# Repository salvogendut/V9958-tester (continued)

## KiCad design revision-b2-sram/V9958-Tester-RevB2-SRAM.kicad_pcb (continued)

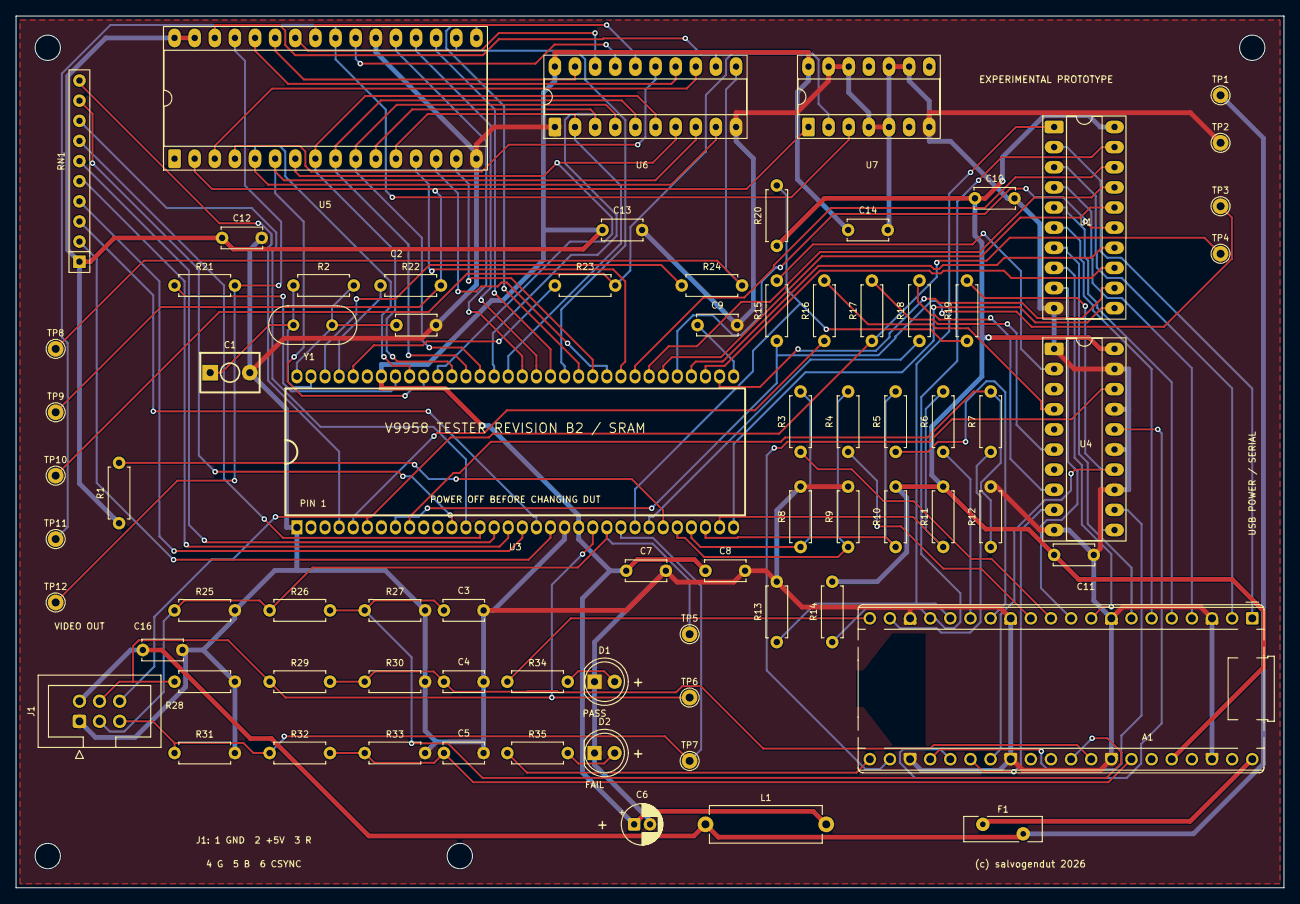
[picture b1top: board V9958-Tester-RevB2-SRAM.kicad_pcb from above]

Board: 2 copper layers, 160.0 x 110.0 mm, 80 parts (0 on the bottom side), 104 nets.

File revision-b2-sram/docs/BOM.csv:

Quantity,References,Value / part,KiCad footprint
1,A1,Raspberry Pi Pico,Module:RaspberryPi_Pico_Common_THT
1,C1,30pF trimmer,V9958-Tester:C_Trim_P5.00mm
1,C10,100n U1,Capacitor_THT:C_Disc_D5.0mm_W2.5mm_P5.00mm
1,C11,100n U4,Capacitor_THT:C_Disc_D5.0mm_W2.5mm_P5.00mm
1,C12,100n SRAM,Capacitor_THT:C_Disc_D5.0mm_W2.5mm_P5.00mm
1,C13,100n U6,Capacitor_THT:C_Disc_D5.0mm_W2.5mm_P5.00mm
1,C14,100n U7,Capacitor_THT:C_Disc_D5.0mm_W2.5mm_P5.00mm
1,C16,100n VIDEO,Capacitor_THT:C_Disc_D5.0mm_W2.5mm_P5.00mm
1,C2,22pF,Capacitor_THT:C_Disc_D5.0mm_W2.5mm_P5.00mm
3,C3 C4 C5,10n,Capacitor_THT:C_Disc_D5.0mm_W2.5mm_P5.00mm
1,C6,100uF,Capacitor_THT:CP_Radial_D5.0mm_P2.00mm
1,C7,100n VDP,Capacitor_THT:C_Disc_D5.0mm_W2.5mm_P5.00mm
1,C8,100n DAC,Capacitor_THT:C_Disc_D5.0mm_W2.5mm_P5.00mm
1,C9,100n VBB,Capacitor_THT:C_Disc_D5.0mm_W2.5mm_P5.00mm
1,D1,GREEN PASS,LED_THT:LED_D5.0mm
1,D2,RED FAIL,LED_THT:LED_D5.0mm
1,F1,Bourns MF-RHT100 PTC 1.0A,Fuse:Fuse_Bourns_MF-RHT100
1,J1,VIDEO DAUGHTERBOARD,Connector_IDC:IDC-Header_2x03_P2.54mm_Vertical
1,L1,5.6uH,Inductor_THT:L_Axial_L14.0mm_D4.5mm_P15.24mm_Horizontal_Fastron_LACC
9,R1 R8 R9 R10 R11 R12 R13 R14 R20,10k,Resistor_THT:R_Axial_DIN0207_L6.3mm_D2.5mm_P7.62mm_Horizontal
7,R15 R16 R17 R18 R19 R34 R35,1k,Resistor_THT:R_Axial_DIN0207_L6.3mm_D2.5mm_P7.62mm_Horizontal
1,R2,470k,Resistor_THT:R_Axial_DIN0207_L6.3mm_D2.5mm_P7.62mm_Horizontal
4,R21 R22 R23 R24,47,Resistor_THT:R_Axial_DIN0207_L6.3mm_D2.5mm_P7.62mm_Horizontal
3,R25 R28 R31,470,Resistor_THT:R_Axial_DIN0207_L6.3mm_D2.5mm_P7.62mm_Horizontal
6,R26 R27 R29 R30 R32 R33,22k,Resistor_THT:R_Axial_DIN0207_L6.3mm_D2.5mm_P7.62mm_Horizontal
5,R3 R4 R5 R6 R7,330,Resistor_THT:R_Axial_DIN0207_L6.3mm_D2.5mm_P7.62mm_Horizontal
1,RN1,10k bussed,Resistor_THT:R_Array_SIP10
1,U1,SN74LVC245AN,Package_DIP:DIP-20_W7.62mm_Socket_LongPads
1,U3,V9958 DUT,V9958-Tester:SDIP-64_W19.05mm_P1.778mm_Socket
1,U4,SN74LVC244AN,Package_DIP:DIP-20_W7.62mm_Socket_LongPads
1,U5,AS6C1008-55PCN 128Kx8 SRAM,Package_DIP:DIP-32_W15.24mm_Socket_LongPads
1,U6,SN74AHCT573N row-address latch,Package_DIP:DIP-20_W7.62mm_Socket_LongPads
1,U7,SN74AHCT08N CAS-to-OE gate,Package_DIP:DIP-14_W7.62mm_Socket_LongPads
1,Y1,21.477270MHz,Crystal:Crystal_HC49-U_Vertical

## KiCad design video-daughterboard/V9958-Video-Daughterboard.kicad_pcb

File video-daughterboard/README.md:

# V9958 RGB DIN daughterboard

This optional all-through-hole 120 x 80 mm board moves the CXA1645P RGB cable
drivers and Omega-compatible DIN-8 connector away from the minimal Revision B
tester core.

J1 uses a keyed straight-through 2x3 IDC cable: 1 GND, 2 +5 V, 3 red, 4 green,
5 blue and 6 CSYNC. J2 follows the Omega RGB assignments: pin 1 GND, pin 3 AV
control, pin 4 composite sync, pin 5 RGB/YS control, pin 6 red, pin 7 green and
pin 8 blue. Pin 2 is unconnected because the tester has no audio source.

The output is native 15.6 kHz PAL RGB, not VGA. The board does not create
composite video; J2 pin 4 is sync only. See the [schematic PDF](docs/V9958-Video-Daughterboard-Schematic.pdf),
[BOM](docs/BOM.csv), [test procedure](docs/TEST-PROCEDURE.md) and
[validation record](docs/VALIDATION.md). This remains an unbuilt prototype.

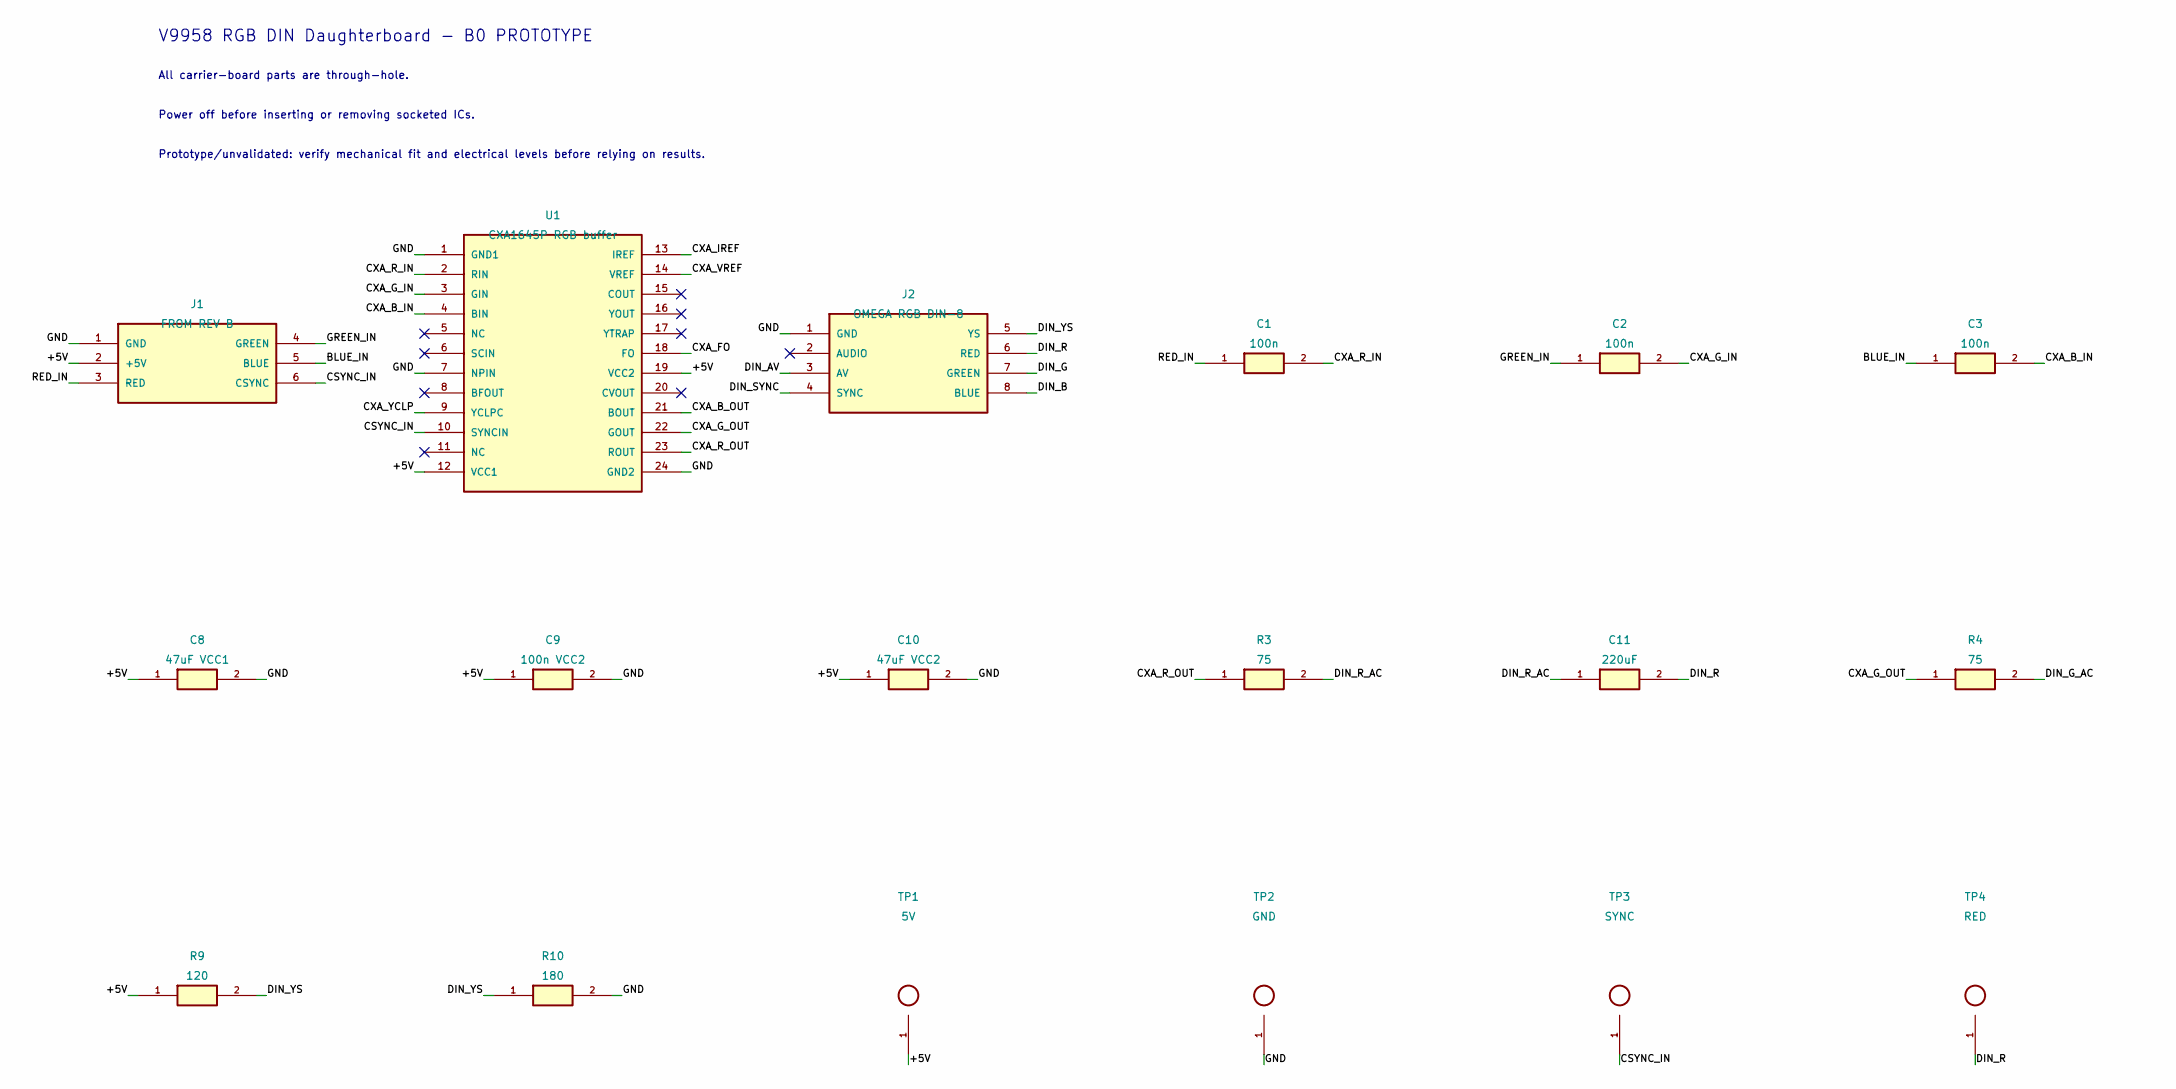
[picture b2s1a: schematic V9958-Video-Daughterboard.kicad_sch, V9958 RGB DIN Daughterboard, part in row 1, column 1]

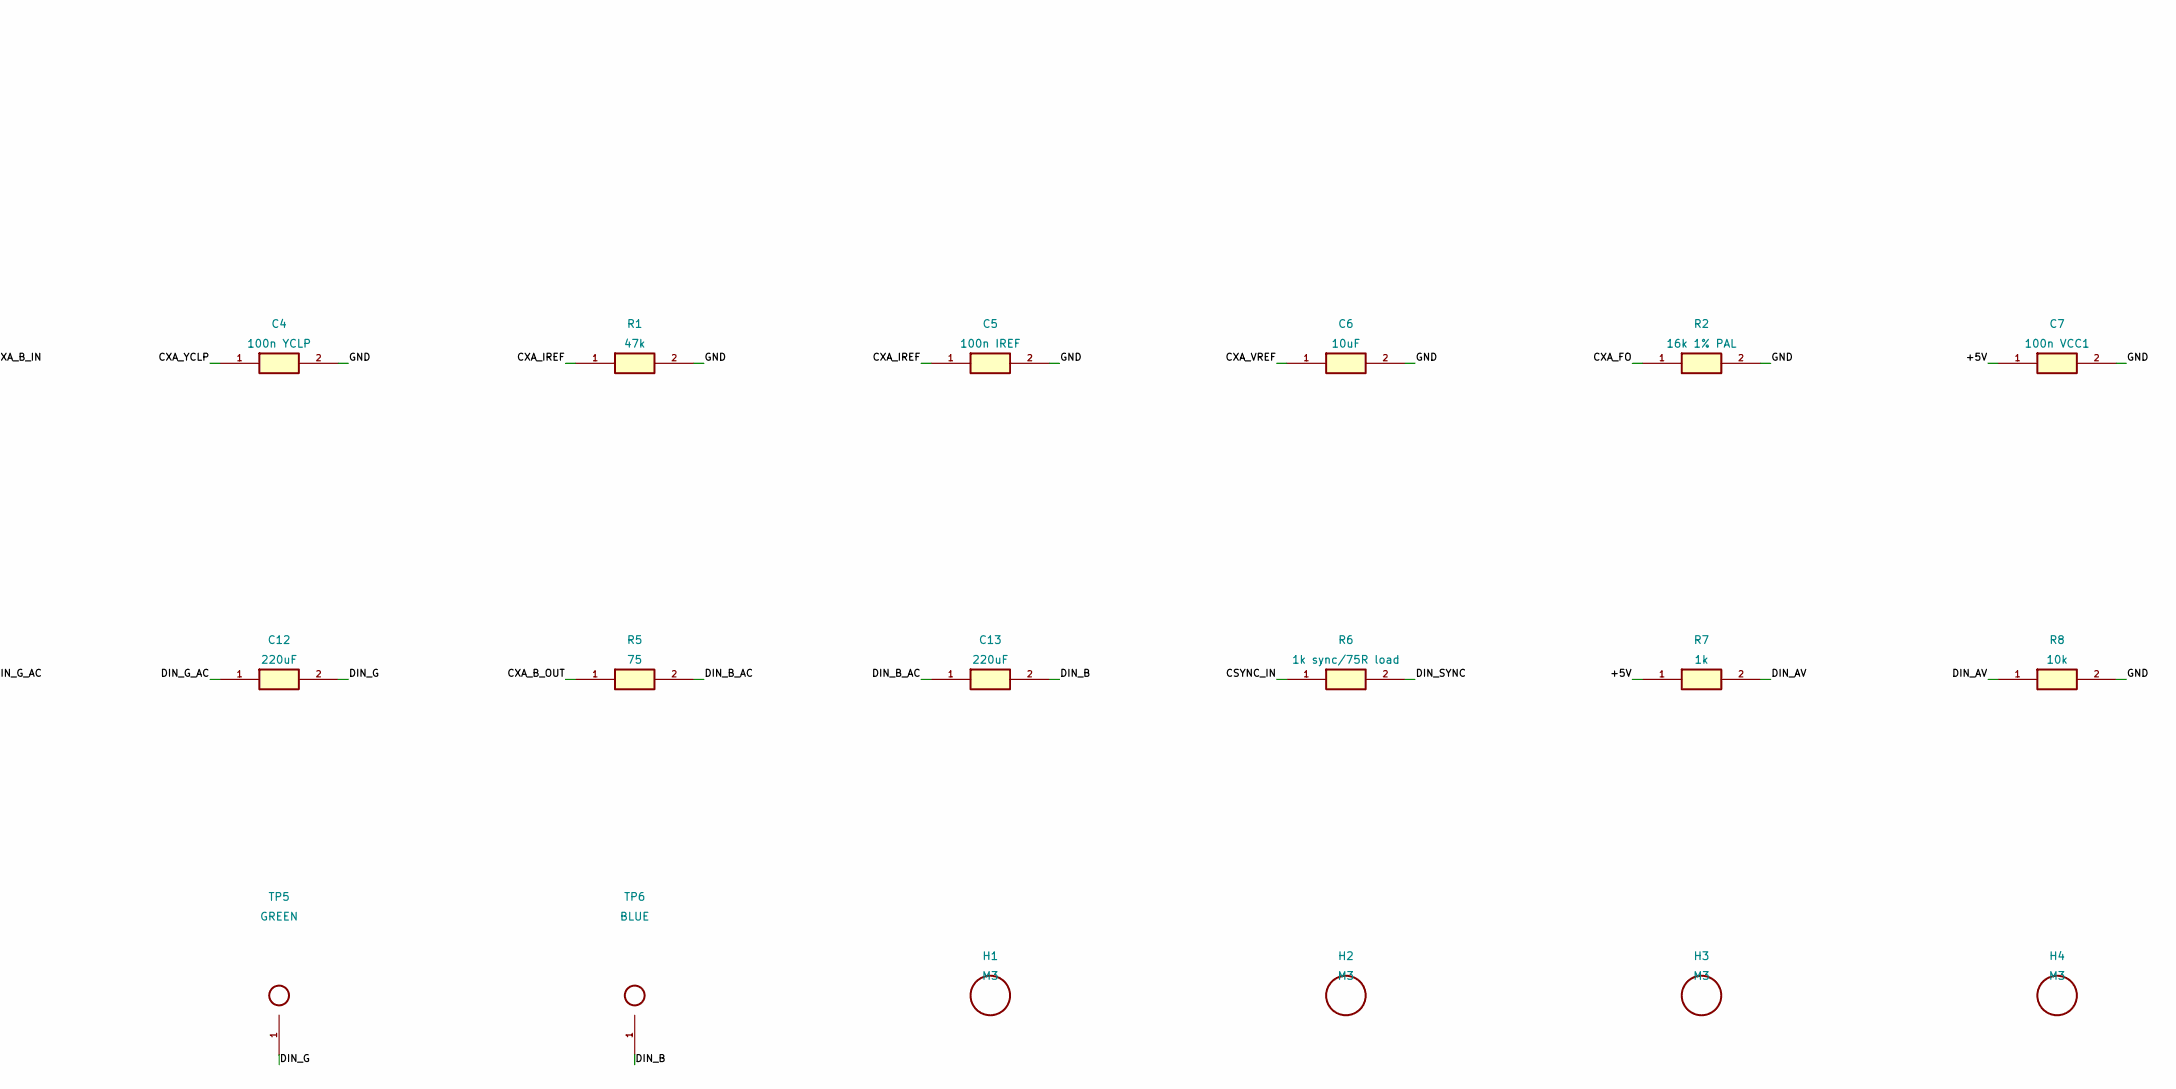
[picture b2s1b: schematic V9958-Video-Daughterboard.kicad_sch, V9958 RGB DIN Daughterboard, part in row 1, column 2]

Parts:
C1, C2, C3: 100n; C_Disc_D5.0mm_W2.5mm_P5.00mm
C4: 100n YCLP; C_Disc_D5.0mm_W2.5mm_P5.00mm
C5: 100n IREF; C_Disc_D5.0mm_W2.5mm_P5.00mm
C6: 10uF; CP_Radial_D5.0mm_P2.00mm
C7: 100n VCC1; C_Disc_D5.0mm_W2.5mm_P5.00mm
C8: 47uF VCC1; CP_Radial_D5.0mm_P2.00mm
C9: 100n VCC2; C_Disc_D5.0mm_W2.5mm_P5.00mm
C10: 47uF VCC2; CP_Radial_D5.0mm_P2.00mm
C11, C12, C13: 220uF; CP_Radial_D8.0mm_P3.50mm
H1, H2, H3, H4: M3; MountingHole_3.2mm_M3
J1: FROM REV B; IDC-Header_2x03_P2.54mm_Vertical
J2: OMEGA RGB DIN-8; DIN8_Omega_THT
R1: 47k; R_Axial_DIN0207_L6.3mm_D2.5mm_P7.62mm_Horizontal
R2: 16k 1% PAL; R_Axial_DIN0207_L6.3mm_D2.5mm_P7.62mm_Horizontal
R3, R4, R5: 75; R_Axial_DIN0207_L6.3mm_D2.5mm_P7.62mm_Horizontal
R6: 1k sync/75R load; R_Axial_DIN0207_L6.3mm_D2.5mm_P7.62mm_Horizontal
R7: 1k; R_Axial_DIN0207_L6.3mm_D2.5mm_P7.62mm_Horizontal
R8: 10k; R_Axial_DIN0207_L6.3mm_D2.5mm_P7.62mm_Horizontal
R9: 120; R_Axial_DIN0207_L6.3mm_D2.5mm_P7.62mm_Horizontal
R10: 180; R_Axial_DIN0207_L6.3mm_D2.5mm_P7.62mm_Horizontal
TP1: 5V; TestPoint_THTPad_D2.0mm_Drill1.0mm
TP2: GND; TestPoint_THTPad_D2.0mm_Drill1.0mm
TP3: SYNC; TestPoint_THTPad_D2.0mm_Drill1.0mm
TP4: RED; TestPoint_THTPad_D2.0mm_Drill1.0mm
TP5: GREEN; TestPoint_THTPad_D2.0mm_Drill1.0mm
TP6: BLUE; TestPoint_THTPad_D2.0mm_Drill1.0mm
U1: CXA1645P RGB buffer; DIP-24_W10.16mm_Socket_LongPads

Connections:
/+5V: C7.1, C8.1, C9.1, C10.1, J1.2 (+5V), R7.1, R9.1, TP1.1, U1.12 (VCC1), U1.19 (VCC2)
/BLUE_IN: C3.1, J1.5 (BLUE)
/CSYNC_IN: J1.6 (CSYNC), R6.1, TP3.1, U1.10 (SYNCIN)
/CXA_B_IN: C3.2, U1.4 (BIN)
/CXA_B_OUT: R5.1, U1.21 (BOUT)
/CXA_FO: R2.1, U1.18 (FO)
/CXA_G_IN: C2.2, U1.3 (GIN)
/CXA_G_OUT: R4.1, U1.22 (GOUT)
/CXA_IREF: C5.1, R1.1, U1.13 (IREF)
/CXA_R_IN: C1.2, U1.2 (RIN)
/CXA_R_OUT: R3.1, U1.23 (ROUT)
/CXA_VREF: C6.1, U1.14 (VREF)
/CXA_YCLP: C4.1, U1.9 (YCLPC)
/DIN_AV: J2.3 (AV), R7.2, R8.1
/DIN_B: C13.2, J2.8 (BLUE), TP6.1
/DIN_B_AC: C13.1, R5.2
/DIN_G: C12.2, J2.7 (GREEN), TP5.1
/DIN_G_AC: C12.1, R4.2
/DIN_R: C11.2, J2.6 (RED), TP4.1
/DIN_R_AC: C11.1, R3.2
/DIN_SYNC: J2.4 (SYNC), R6.2
/DIN_YS: J2.5 (YS), R9.2, R10.1
/GND: C4.2, C5.2, C6.2, C7.2, C8.2, C9.2, C10.2, J1.1 (GND), J2.1 (GND), R1.2, R2.2, R8.2, R10.2, TP2.1, U1.1 (GND1), U1.7 (NPIN), U1.24 (GND2)
/GREEN_IN: C2.1, J1.4 (GREEN)
/RED_IN: C1.1, J1.3 (RED)

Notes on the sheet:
V9958 RGB DIN Daughterboard - B0 PROTOTYPE
All carrier-board parts are through-hole.
Power off before inserting or removing socketed ICs.
Prototype/unvalidated: verify mechanical fit and electrical levels before relying on results.

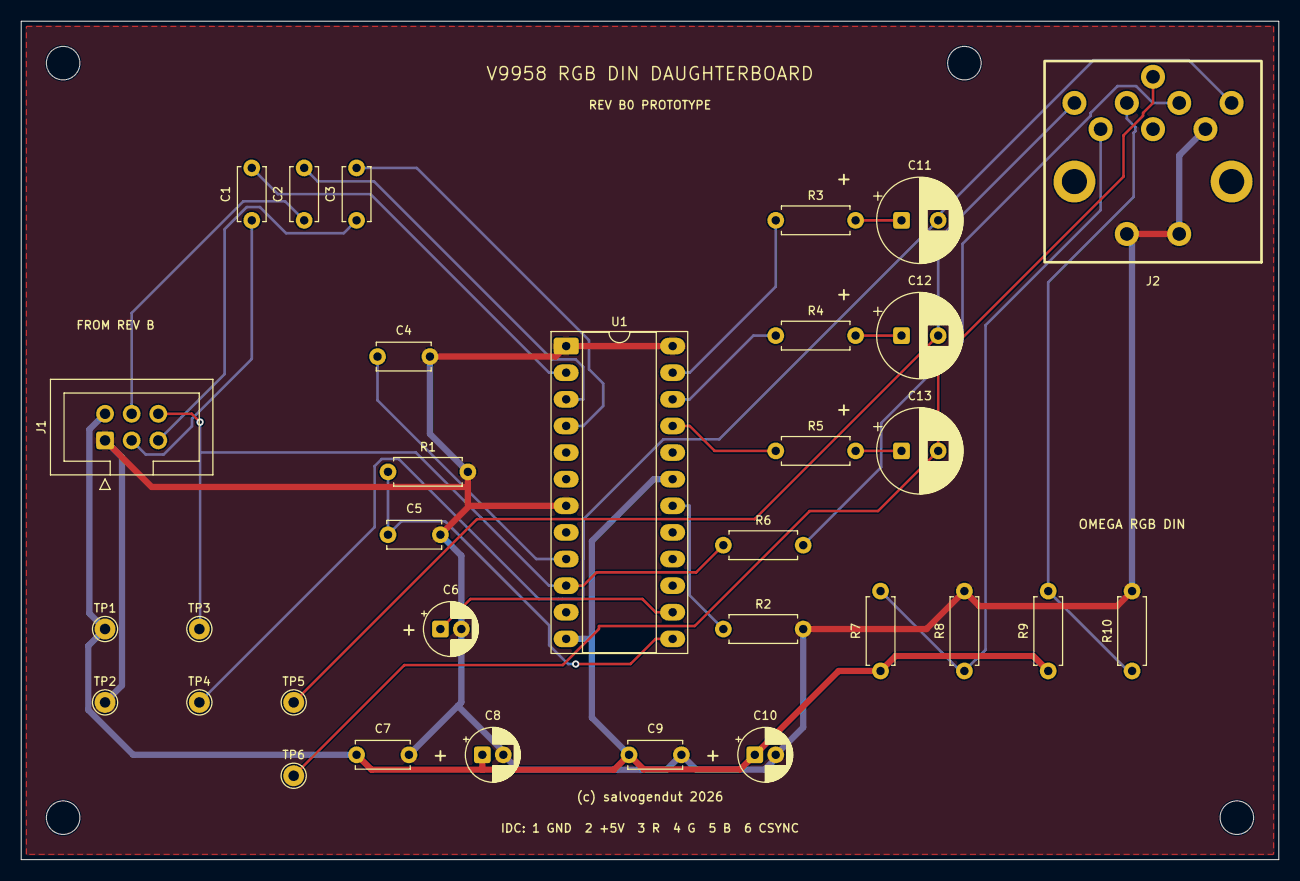
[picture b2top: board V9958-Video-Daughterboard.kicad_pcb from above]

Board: 2 copper layers, 120.0 x 80.0 mm, 36 parts (0 on the bottom side), 25 nets.

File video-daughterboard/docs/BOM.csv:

Quantity,References,Value / part,KiCad footprint
3,C1 C2 C3,100n,Capacitor_THT:C_Disc_D5.0mm_W2.5mm_P5.00mm
1,C10,47uF VCC2,Capacitor_THT:CP_Radial_D5.0mm_P2.00mm
3,C11 C12 C13,220uF,Capacitor_THT:CP_Radial_D8.0mm_P3.50mm
1,C4,100n YCLP,Capacitor_THT:C_Disc_D5.0mm_W2.5mm_P5.00mm
1,C5,100n IREF,Capacitor_THT:C_Disc_D5.0mm_W2.5mm_P5.00mm
1,C6,10uF,Capacitor_THT:CP_Radial_D5.0mm_P2.00mm
1,C7,100n VCC1,Capacitor_THT:C_Disc_D5.0mm_W2.5mm_P5.00mm
1,C8,47uF VCC1,Capacitor_THT:CP_Radial_D5.0mm_P2.00mm
1,C9,100n VCC2,Capacitor_THT:C_Disc_D5.0mm_W2.5mm_P5.00mm
1,J1,FROM REV B,Connector_IDC:IDC-Header_2x03_P2.54mm_Vertical
1,J2,OMEGA RGB DIN-8,V9958-Video-Daughterboard:DIN8_Omega_THT
1,R1,47k,Resistor_THT:R_Axial_DIN0207_L6.3mm_D2.5mm_P7.62mm_Horizontal
1,R10,180,Resistor_THT:R_Axial_DIN0207_L6.3mm_D2.5mm_P7.62mm_Horizontal
1,R2,16k 1% PAL,Resistor_THT:R_Axial_DIN0207_L6.3mm_D2.5mm_P7.62mm_Horizontal
3,R3 R4 R5,75,Resistor_THT:R_Axial_DIN0207_L6.3mm_D2.5mm_P7.62mm_Horizontal
1,R6,1k sync/75R load,Resistor_THT:R_Axial_DIN0207_L6.3mm_D2.5mm_P7.62mm_Horizontal
1,R7,1k,Resistor_THT:R_Axial_DIN0207_L6.3mm_D2.5mm_P7.62mm_Horizontal
1,R8,10k,Resistor_THT:R_Axial_DIN0207_L6.3mm_D2.5mm_P7.62mm_Horizontal
1,R9,120,Resistor_THT:R_Axial_DIN0207_L6.3mm_D2.5mm_P7.62mm_Horizontal
1,U1,CXA1645P RGB buffer,Package_DIP:DIP-24_W10.16mm_Socket_LongPads

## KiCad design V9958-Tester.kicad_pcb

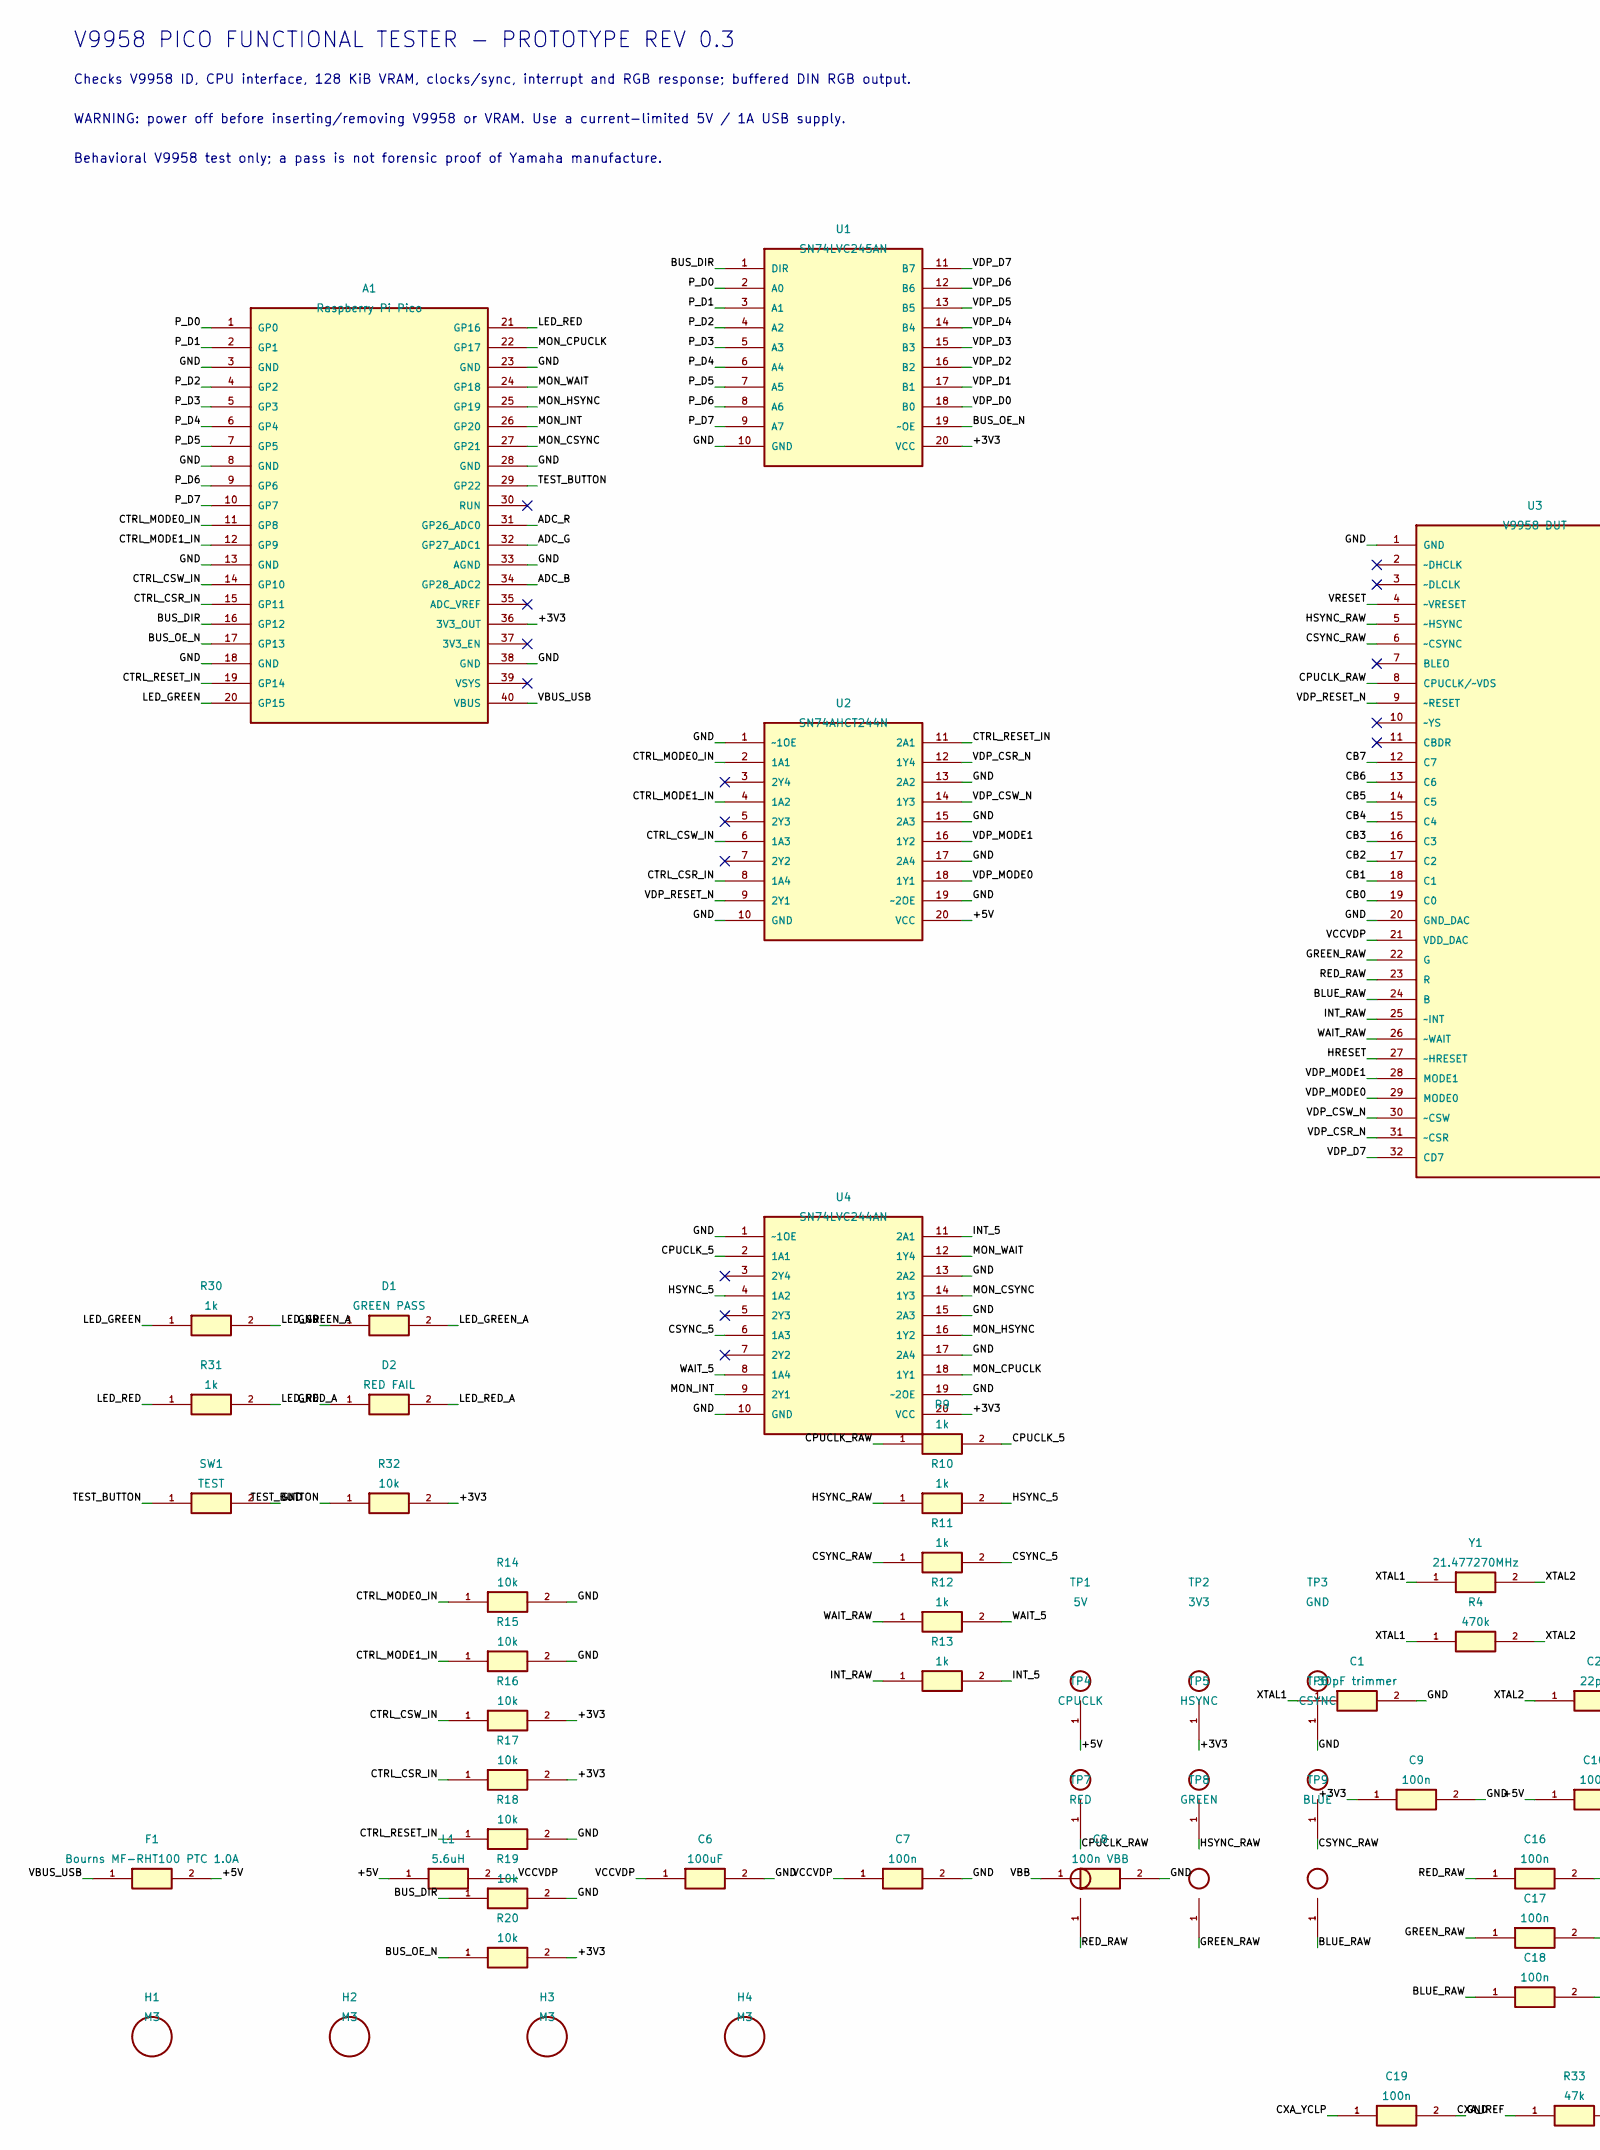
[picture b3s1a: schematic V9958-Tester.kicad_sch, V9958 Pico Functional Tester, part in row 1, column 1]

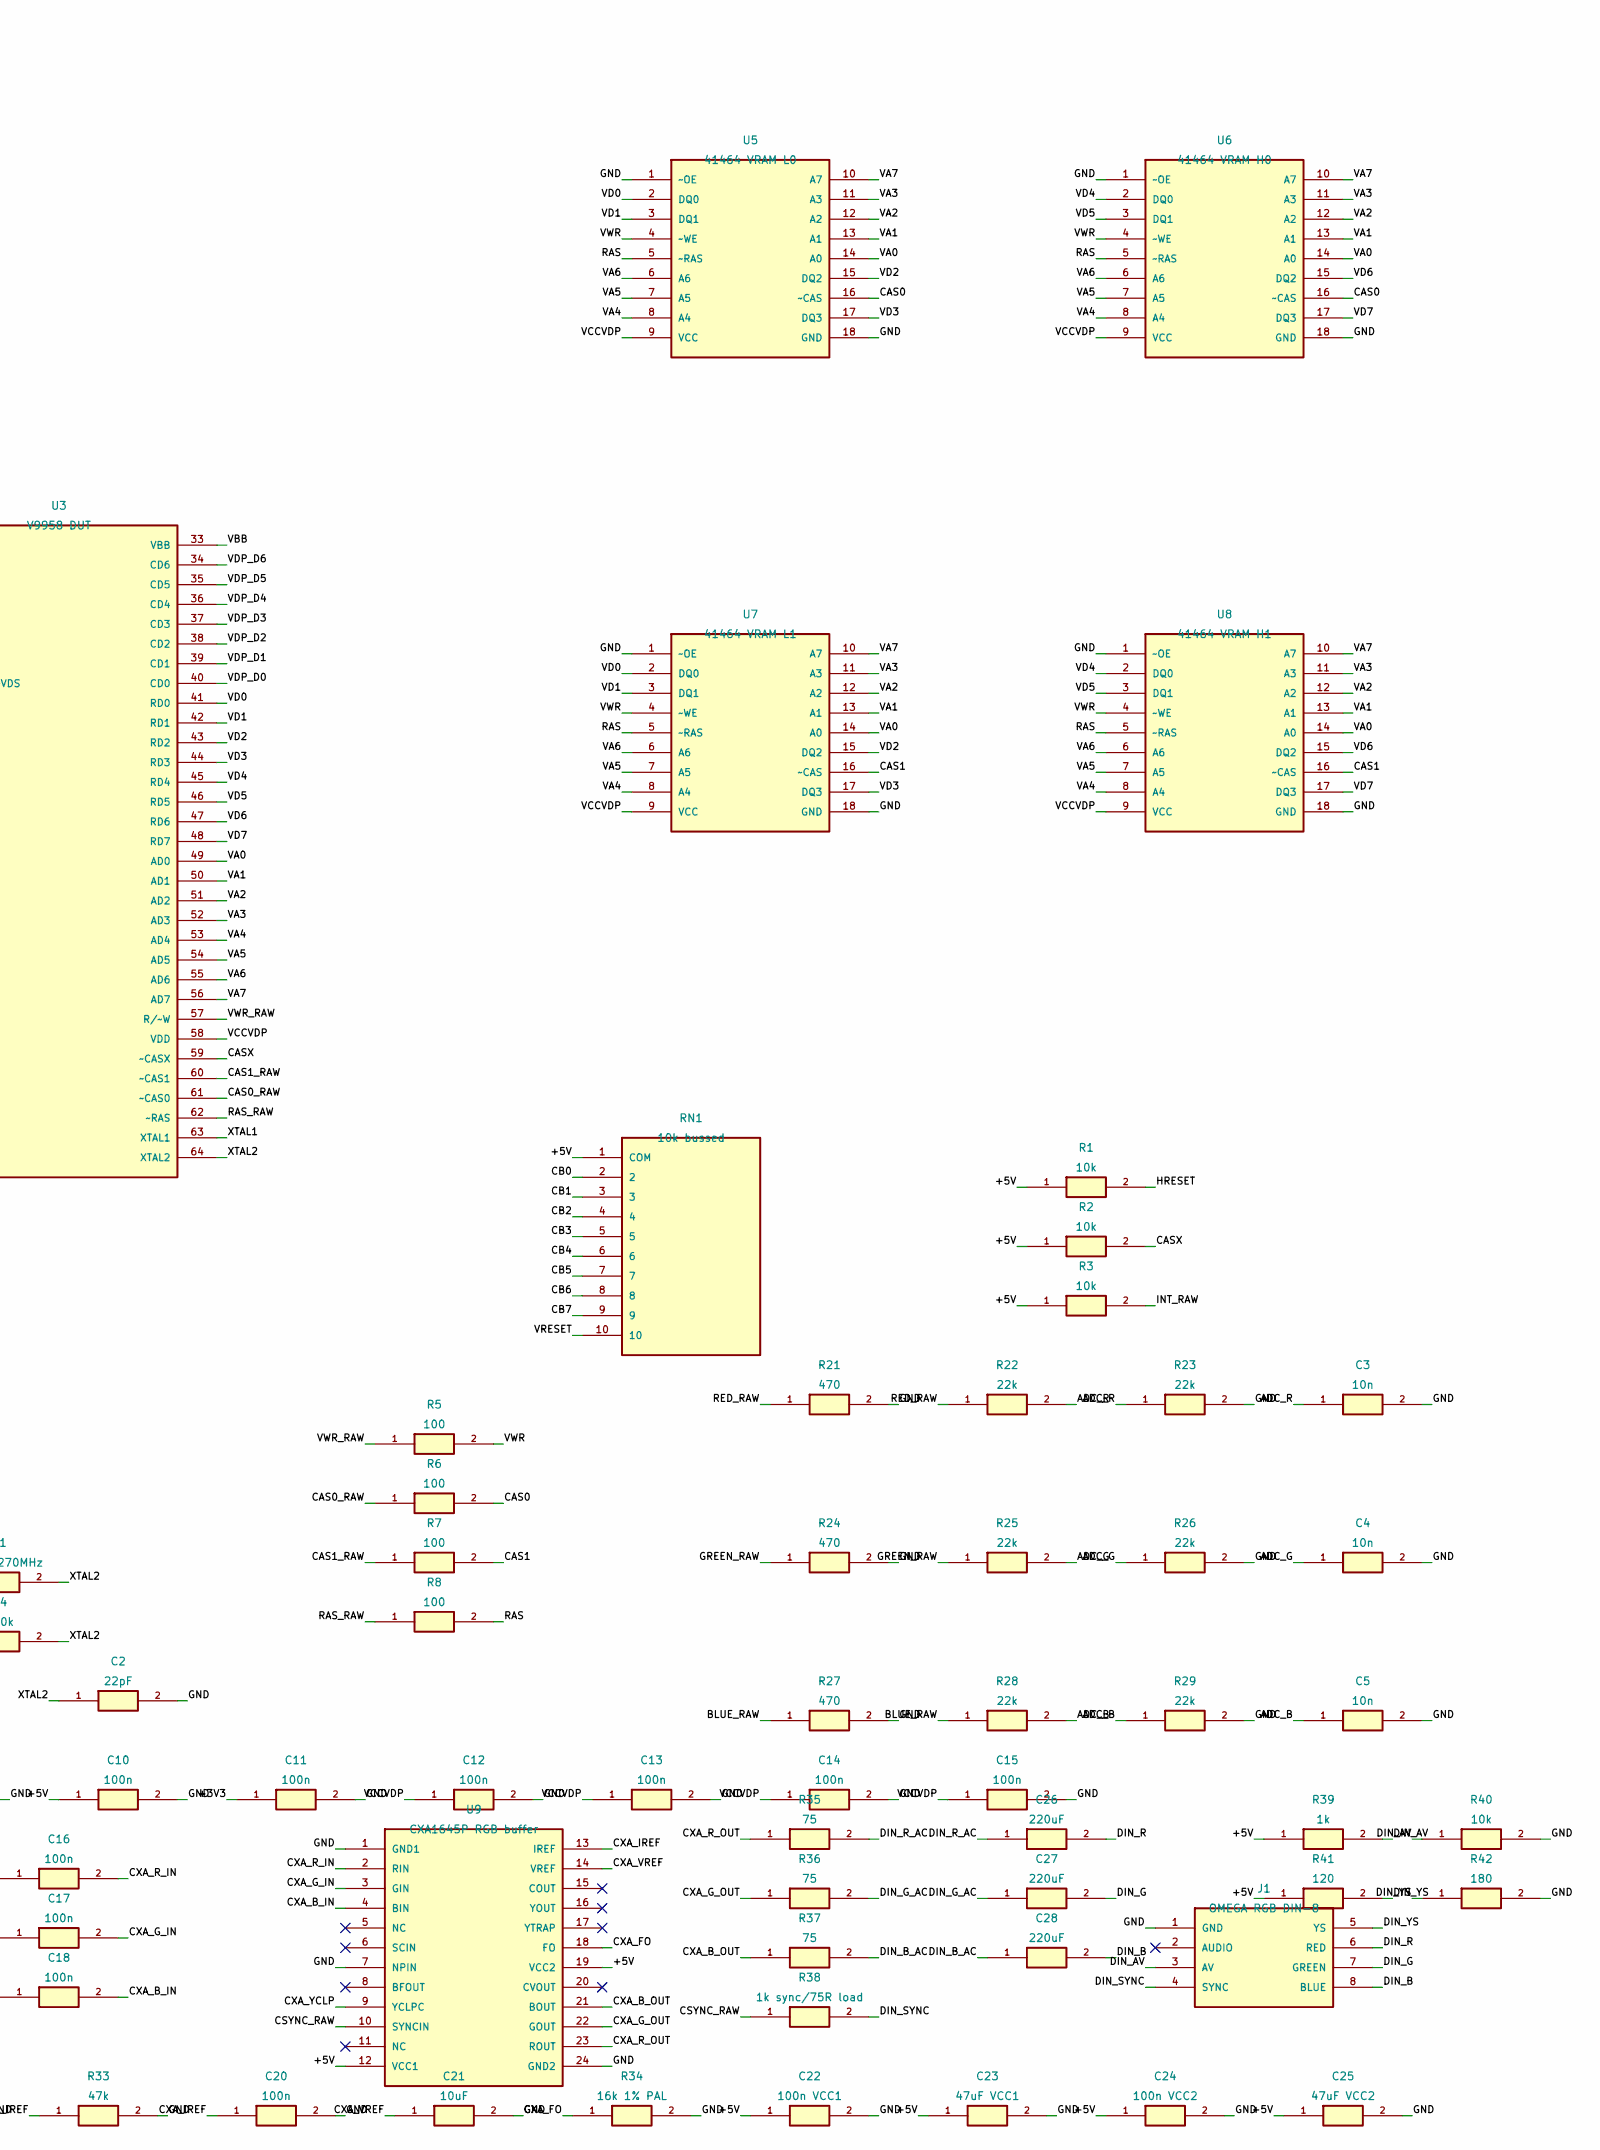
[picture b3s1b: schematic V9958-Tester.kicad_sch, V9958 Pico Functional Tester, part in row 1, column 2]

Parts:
A1: Raspberry Pi Pico; RaspberryPi_Pico_Common_THT
C1: 30pF trimmer; C_Trim_P5.00mm
C2: 22pF; C_Disc_D5.0mm_W2.5mm_P5.00mm
C3, C4, C5: 10n; C_Disc_D5.0mm_W2.5mm_P5.00mm
C6: 100uF; CP_Radial_D5.0mm_P2.00mm
C7, C9, C10, C11, C12, C13, C14, C15, C16, C17, C18, C19, C20: 100n; C_Disc_D5.0mm_W2.5mm_P5.00mm
C8: 100n VBB; C_Disc_D5.0mm_W2.5mm_P5.00mm
C21: 10uF; CP_Radial_D5.0mm_P2.00mm
C22: 100n VCC1; C_Disc_D5.0mm_W2.5mm_P5.00mm
C23: 47uF VCC1; CP_Radial_D5.0mm_P2.00mm
C24: 100n VCC2; C_Disc_D5.0mm_W2.5mm_P5.00mm
C25: 47uF VCC2; CP_Radial_D5.0mm_P2.00mm
C26, C27, C28: 220uF; CP_Radial_D8.0mm_P3.50mm
D1: GREEN PASS; LED_D5.0mm
D2: RED FAIL; LED_D5.0mm
F1: Bourns MF-RHT100 PTC 1.0A; Fuse_Bourns_MF-RHT100
H1, H2, H3, H4: M3; MountingHole_3.2mm_M3
J1: OMEGA RGB DIN-8; DIN8_Omega_THT
L1: 5.6uH; L_Axial_L14.0mm_D4.5mm_P15.24mm_Horizontal_Fastron_LACC
R1, R2, R3, R14, R15, R16, R17, R18, R19, R20, R32, R40: 10k; R_Axial_DIN0207_L6.3mm_D2.5mm_P7.62mm_Horizontal
R4: 470k; R_Axial_DIN0207_L6.3mm_D2.5mm_P7.62mm_Horizontal
R5, R6, R7, R8: 100; R_Axial_DIN0207_L6.3mm_D2.5mm_P7.62mm_Horizontal
R9, R10, R11, R12, R13, R30, R31, R39: 1k; R_Axial_DIN0207_L6.3mm_D2.5mm_P7.62mm_Horizontal
R21, R24, R27: 470; R_Axial_DIN0207_L6.3mm_D2.5mm_P7.62mm_Horizontal
R22, R23, R25, R26, R28, R29: 22k; R_Axial_DIN0207_L6.3mm_D2.5mm_P7.62mm_Horizontal
R33: 47k; R_Axial_DIN0207_L6.3mm_D2.5mm_P7.62mm_Horizontal
R34: 16k 1% PAL; R_Axial_DIN0207_L6.3mm_D2.5mm_P7.62mm_Horizontal
R35, R36, R37: 75; R_Axial_DIN0207_L6.3mm_D2.5mm_P7.62mm_Horizontal
R38: 1k sync/75R load; R_Axial_DIN0207_L6.3mm_D2.5mm_P7.62mm_Horizontal
R41: 120; R_Axial_DIN0207_L6.3mm_D2.5mm_P7.62mm_Horizontal
R42: 180; R_Axial_DIN0207_L6.3mm_D2.5mm_P7.62mm_Horizontal
RN1: 10k bussed; R_Array_SIP10
SW1: TEST; SW_PUSH_6mm_H7.3mm
TP1: 5V; TestPoint_THTPad_D2.0mm_Drill1.0mm
TP2: 3V3; TestPoint_THTPad_D2.0mm_Drill1.0mm
TP3: GND; TestPoint_THTPad_D2.0mm_Drill1.0mm
TP4: CPUCLK; TestPoint_THTPad_D2.0mm_Drill1.0mm
TP5: HSYNC; TestPoint_THTPad_D2.0mm_Drill1.0mm
TP6: CSYNC; TestPoint_THTPad_D2.0mm_Drill1.0mm
TP7: RED; TestPoint_THTPad_D2.0mm_Drill1.0mm
TP8: GREEN; TestPoint_THTPad_D2.0mm_Drill1.0mm
TP9: BLUE; TestPoint_THTPad_D2.0mm_Drill1.0mm
U1: SN74LVC245AN; DIP-20_W7.62mm_Socket_LongPads
U2: SN74AHCT244N; DIP-20_W7.62mm_Socket_LongPads
U3: V9958 DUT; SDIP-64_W19.05mm_P1.778mm_Socket
U4: SN74LVC244AN; DIP-20_W7.62mm_Socket_LongPads
U5: 41464 VRAM L0; DIP-18_W7.62mm_Socket_LongPads
U6: 41464 VRAM H0; DIP-18_W7.62mm_Socket_LongPads
U7: 41464 VRAM L1; DIP-18_W7.62mm_Socket_LongPads
U8: 41464 VRAM H1; DIP-18_W7.62mm_Socket_LongPads
U9: CXA1645P RGB buffer; DIP-24_W10.16mm_Socket_LongPads
Y1: 21.477270MHz; Crystal_HC49-U_Vertical

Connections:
/+3V3: A1.36 (3V3_OUT), C9.1, C11.1, R16.2, R17.2, R20.2, R32.2, TP2.1, U1.20 (VCC), U4.20 (VCC)
/+5V: C10.1, C22.1, C23.1, C24.1, C25.1, F1.2, L1.1, R1.1, R2.1, R3.1, R39.1, R41.1, RN1.1 (COM), TP1.1, U2.20 (VCC), U9.12 (VCC1), U9.19 (VCC2)
/ADC_B: A1.34 (GP28_ADC2), C5.1, R28.2, R29.1
/ADC_G: A1.32 (GP27_ADC1), C4.1, R25.2, R26.1
/ADC_R: A1.31 (GP26_ADC0), C3.1, R22.2, R23.1
/BLUE_RAW: C18.1, R27.1, R28.1, TP9.1, U3.24 (B)
/BUS_DIR: A1.16 (GP12), R19.1, U1.1 (DIR)
/BUS_OE_N: A1.17 (GP13), R20.1, U1.19 (~OE)
/CAS0: R6.2, U5.16 (~CAS), U6.16 (~CAS)
/CAS0_RAW: R6.1, U3.61 (~CAS0)
/CAS1: R7.2, U7.16 (~CAS), U8.16 (~CAS)
/CAS1_RAW: R7.1, U3.60 (~CAS1)
/CASX: R2.2, U3.59 (~CASX)
/CB0: RN1.2, U3.19 (C0)
/CB1: RN1.3, U3.18 (C1)
/CB2: RN1.4, U3.17 (C2)
/CB3: RN1.5, U3.16 (C3)
/CB4: RN1.6, U3.15 (C4)
/CB5: RN1.7, U3.14 (C5)
/CB6: RN1.8, U3.13 (C6)
/CB7: RN1.9, U3.12 (C7)
/CPUCLK_5: R9.2, U4.2 (1A1)
/CPUCLK_RAW: R9.1, TP4.1, U3.8 (CPUCLK/~VDS)
/CSYNC_5: R11.2, U4.6 (1A3)
/CSYNC_RAW: R11.1, R38.1, TP6.1, U3.6 (~CSYNC), U9.10 (SYNCIN)
/CTRL_CSR_IN: A1.15 (GP11), R17.1, U2.8 (1A4)
/CTRL_CSW_IN: A1.14 (GP10), R16.1, U2.6 (1A3)
/CTRL_MODE0_IN: A1.11 (GP8), R14.1, U2.2 (1A1)
/CTRL_MODE1_IN: A1.12 (GP9), R15.1, U2.4 (1A2)
/CTRL_RESET_IN: A1.19 (GP14), R18.1, U2.11 (2A1)
/CXA_B_IN: C18.2, U9.4 (BIN)
/CXA_B_OUT: R37.1, U9.21 (BOUT)
/CXA_FO: R34.1, U9.18 (FO)
/CXA_G_IN: C17.2, U9.3 (GIN)
/CXA_G_OUT: R36.1, U9.22 (GOUT)
/CXA_IREF: C20.1, R33.1, U9.13 (IREF)
/CXA_R_IN: C16.2, U9.2 (RIN)
/CXA_R_OUT: R35.1, U9.23 (ROUT)
/CXA_VREF: C21.1, U9.14 (VREF)
/CXA_YCLP: C19.1, U9.9 (YCLPC)
/DIN_AV: J1.3 (AV), R39.2, R40.1
/DIN_B: C28.2, J1.8 (BLUE)
/DIN_B_AC: C28.1, R37.2
/DIN_G: C27.2, J1.7 (GREEN)
/DIN_G_AC: C27.1, R36.2
/DIN_R: C26.2, J1.6 (RED)
/DIN_R_AC: C26.1, R35.2
/DIN_SYNC: J1.4 (SYNC), R38.2
/DIN_YS: J1.5 (YS), R41.2, R42.1
/GND: A1.3 (GND), A1.8 (GND), A1.13 (GND), A1.18 (GND), A1.23 (GND), A1.28 (GND), A1.33 (AGND), A1.38 (GND), C1.2, C2.2, C3.2, C4.2, C5.2, C6.2, C7.2, C8.2, C9.2, C10.2, C11.2, C12.2, C13.2, C14.2, C15.2, C19.2, C20.2, C21.2, C22.2, C23.2, C24.2, C25.2, D1.1, D2.1, J1.1 (GND), R14.2, R15.2, R18.2, R19.2, R21.2, R23.2, R24.2, R26.2, R27.2, R29.2, R33.2, R34.2, R40.2, R42.2, SW1.2, TP3.1, U1.10 (GND), U2.1 (~1OE), U2.10 (GND), U2.13 (2A2), U2.15 (2A3), U2.17 (2A4), U2.19 (~2OE), U3.1 (GND), U3.20 (GND_DAC), U4.1 (~1OE), U4.10 (GND), U4.13 (2A2), U4.15 (2A3), U4.17 (2A4), U4.19 (~2OE), U5.1 (~OE), U5.18 (GND), U6.1 (~OE), U6.18 (GND), U7.1 (~OE), U7.18 (GND), U8.1 (~OE), U8.18 (GND), U9.1 (GND1), U9.7 (NPIN), U9.24 (GND2)
/GREEN_RAW: C17.1, R24.1, R25.1, TP8.1, U3.22 (G)
/HRESET: R1.2, U3.27 (~HRESET)
/HSYNC_5: R10.2, U4.4 (1A2)
/HSYNC_RAW: R10.1, TP5.1, U3.5 (~HSYNC)
/INT_5: R13.2, U4.11 (2A1)
/INT_RAW: R3.2, R13.1, U3.25 (~INT)
/LED_GREEN: A1.20 (GP15), R30.1
/LED_GREEN_A: D1.2, R30.2
/LED_RED: A1.21 (GP16), R31.1
/LED_RED_A: D2.2, R31.2
/MON_CPUCLK: A1.22 (GP17), U4.18 (1Y1)
/MON_CSYNC: A1.27 (GP21), U4.14 (1Y3)
/MON_HSYNC: A1.25 (GP19), U4.16 (1Y2)
/MON_INT: A1.26 (GP20), U4.9 (2Y1)
/MON_WAIT: A1.24 (GP18), U4.12 (1Y4)
/P_D0: A1.1 (GP0), U1.2 (A0)
/P_D1: A1.2 (GP1), U1.3 (A1)
/P_D2: A1.4 (GP2), U1.4 (A2)
/P_D3: A1.5 (GP3), U1.5 (A3)
/P_D4: A1.6 (GP4), U1.6 (A4)
/P_D5: A1.7 (GP5), U1.7 (A5)
/P_D6: A1.9 (GP6), U1.8 (A6)
/P_D7: A1.10 (GP7), U1.9 (A7)
/RAS: R8.2, U5.5 (~RAS), U6.5 (~RAS), U7.5 (~RAS), U8.5 (~RAS)
/RAS_RAW: R8.1, U3.62 (~RAS)
/RED_RAW: C16.1, R21.1, R22.1, TP7.1, U3.23 (R)
/TEST_BUTTON: A1.29 (GP22), R32.1, SW1.1
/VA0: U3.49 (AD0), U5.14 (A0), U6.14 (A0), U7.14 (A0), U8.14 (A0)
/VA1: U3.50 (AD1), U5.13 (A1), U6.13 (A1), U7.13 (A1), U8.13 (A1)
/VA2: U3.51 (AD2), U5.12 (A2), U6.12 (A2), U7.12 (A2), U8.12 (A2)
/VA3: U3.52 (AD3), U5.11 (A3), U6.11 (A3), U7.11 (A3), U8.11 (A3)
/VA4: U3.53 (AD4), U5.8 (A4), U6.8 (A4), U7.8 (A4), U8.8 (A4)
/VA5: U3.54 (AD5), U5.7 (A5), U6.7 (A5), U7.7 (A5), U8.7 (A5)
/VA6: U3.55 (AD6), U5.6 (A6), U6.6 (A6), U7.6 (A6), U8.6 (A6)
/VA7: U3.56 (AD7), U5.10 (A7), U6.10 (A7), U7.10 (A7), U8.10 (A7)
/VBB: C8.1, U3.33 (VBB)
/VBUS_USB: A1.40 (VBUS), F1.1
/VCCVDP: C6.1, C7.1, C12.1, C13.1, C14.1, C15.1, L1.2, U3.21 (VDD_DAC), U3.58 (VDD), U5.9 (VCC), U6.9 (VCC), U7.9 (VCC), U8.9 (VCC)
/VD0: U3.41 (RD0), U5.2 (DQ0), U7.2 (DQ0)
/VD1: U3.42 (RD1), U5.3 (DQ1), U7.3 (DQ1)
/VD2: U3.43 (RD2), U5.15 (DQ2), U7.15 (DQ2)
/VD3: U3.44 (RD3), U5.17 (DQ3), U7.17 (DQ3)
/VD4: U3.45 (RD4), U6.2 (DQ0), U8.2 (DQ0)
/VD5: U3.46 (RD5), U6.3 (DQ1), U8.3 (DQ1)
/VD6: U3.47 (RD6), U6.15 (DQ2), U8.15 (DQ2)
/VD7: U3.48 (RD7), U6.17 (DQ3), U8.17 (DQ3)
/VDP_CSR_N: U2.12 (1Y4), U3.31 (~CSR)
/VDP_CSW_N: U2.14 (1Y3), U3.30 (~CSW)
/VDP_D0: U1.18 (B0), U3.40 (CD0)
/VDP_D1: U1.17 (B1), U3.39 (CD1)
/VDP_D2: U1.16 (B2), U3.38 (CD2)
/VDP_D3: U1.15 (B3), U3.37 (CD3)
/VDP_D4: U1.14 (B4), U3.36 (CD4)
/VDP_D5: U1.13 (B5), U3.35 (CD5)
/VDP_D6: U1.12 (B6), U3.34 (CD6)
/VDP_D7: U1.11 (B7), U3.32 (CD7)
/VDP_MODE0: U2.18 (1Y1), U3.29 (MODE0)
/VDP_MODE1: U2.16 (1Y2), U3.28 (MODE1)
/VDP_RESET_N: U2.9 (2Y1), U3.9 (~RESET)
/VRESET: RN1.10, U3.4 (~VRESET)
/VWR: R5.2, U5.4 (~WE), U6.4 (~WE), U7.4 (~WE), U8.4 (~WE)
/VWR_RAW: R5.1, U3.57 (R/~W)
/WAIT_5: R12.2, U4.8 (1A4)
/WAIT_RAW: R12.1, U3.26 (~WAIT)
/XTAL1: C1.1, R4.1, U3.63 (XTAL1), Y1.1
/XTAL2: C2.1, R4.2, U3.64 (XTAL2), Y1.2

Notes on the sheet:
V9958 PICO FUNCTIONAL TESTER - PROTOTYPE REV 0.3
Checks V9958 ID, CPU interface, 128 KiB VRAM, clocks/sync, interrupt and RGB response; buffered DIN RGB output.
WARNING: power off before inserting/removing V9958 or VRAM. Use a current-limited 5V / 1A USB supply.
Behavioral V9958 test only; a pass is not forensic proof of Yamaha manufacture.
